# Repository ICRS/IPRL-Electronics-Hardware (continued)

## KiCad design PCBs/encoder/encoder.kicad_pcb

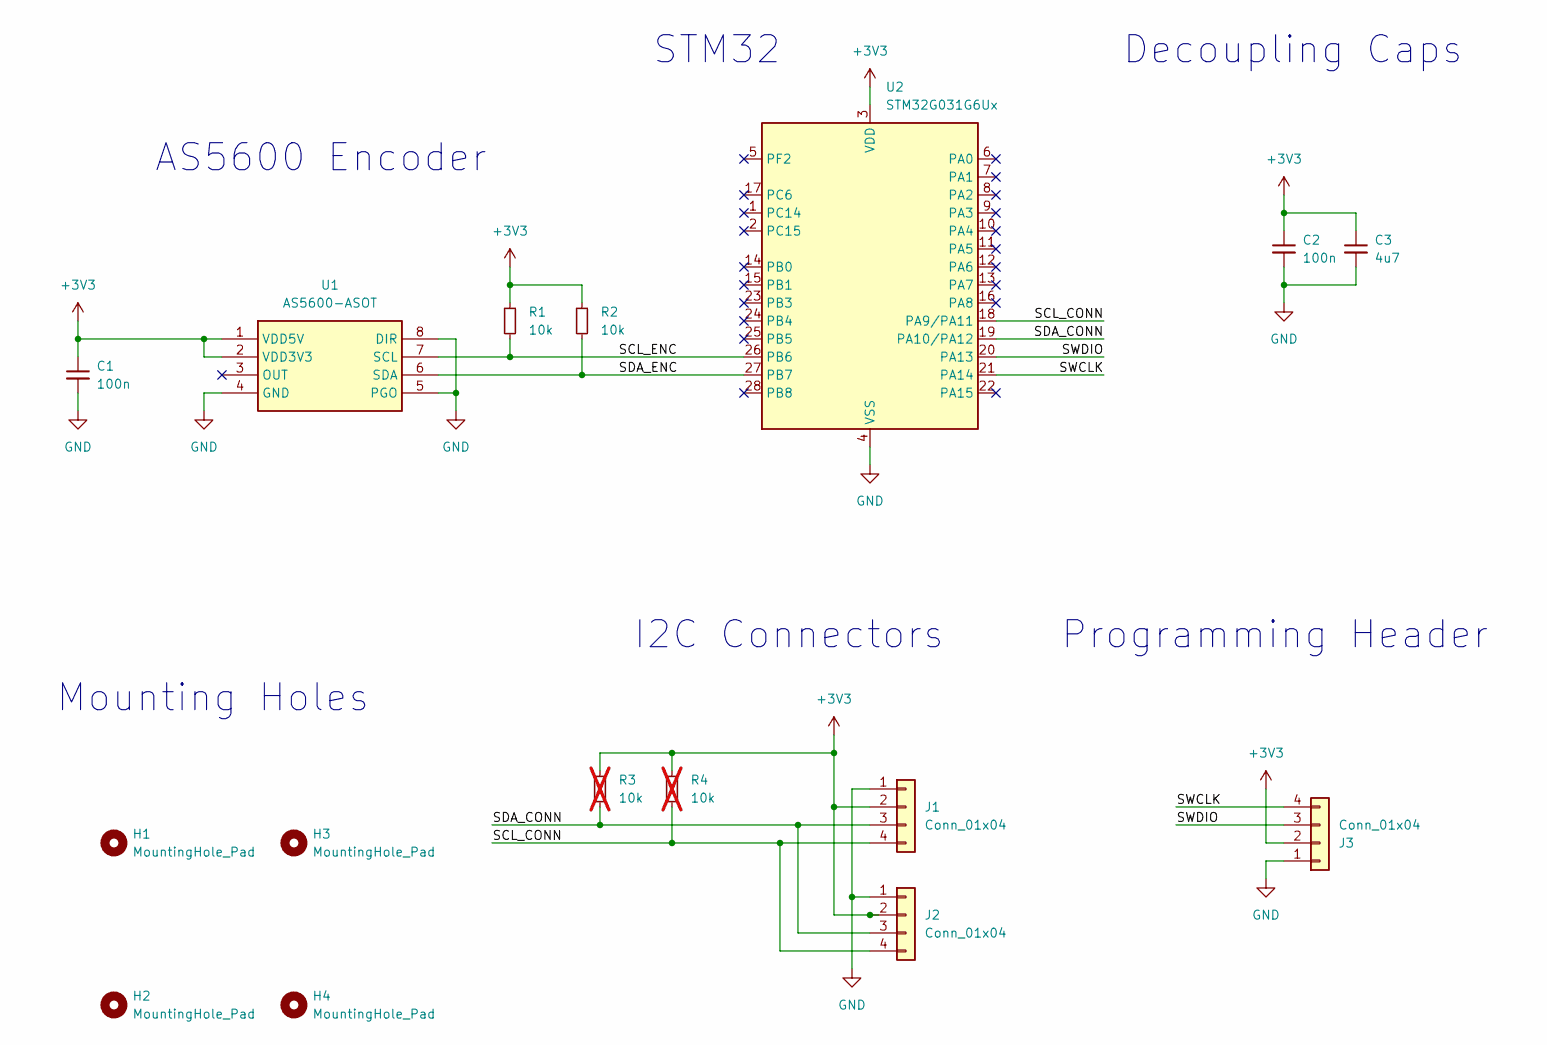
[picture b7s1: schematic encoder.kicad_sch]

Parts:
C1, C2: 100n; C_0603_1608Metric
C3: 4u7; C_0603_1608Metric
H1, H2, H3, H4: MountingHole_Pad; MountingHole_3.2mm_M3
J1, J2: Conn_01x04; JST_XH_B4B-XH-A_1x04_P2.50mm_Vertical
J3: Conn_01x04; JST_GH_SM04B-GHS-TB_1x04-1MP_P1.25mm_Horizontal
R1, R2: 10k; R_0603_1608Metric
R3, R4: 10k; R_0603_1608Metric; not fitted
U1: AS5600-ASOT; SOIC127P600X175-8N; Mouser Part Number 985-AS5600-ASOT
U2: STM32G031G6Ux; QFN-28_4x4mm_P0.5mm

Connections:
+3V3: C1.1, C2.1, C3.1, J1.2, J2.2, J3.2, R1.1, R2.1, R3.1, R4.1, U1.1 (VDD5V), U1.2 (VDD3V3), U2.3 (VDD)
/SCL_CONN: J1.4, J2.4, R4.2, U2.18 (PA9/PA11)
/SCL_ENC: R1.2, U1.7 (SCL), U2.26 (PB6)
/SDA_CONN: J1.3, J2.3, R3.2, U2.19 (PA10/PA12)
/SDA_ENC: R2.2, U1.6 (SDA), U2.27 (PB7)
/SWCLK: J3.4, U2.21 (PA14)
/SWDIO: J3.3, U2.20 (PA13)
GND: C1.2, C2.2, C3.2, J1.1, J2.1, J3.1, U1.4 (GND), U1.5 (PGO), U1.8 (DIR), U2.4 (VSS)

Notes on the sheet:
Mounting Holes
I2C Connectors
STM32
Programming Header
Decoupling Caps
AS5600 Encoder

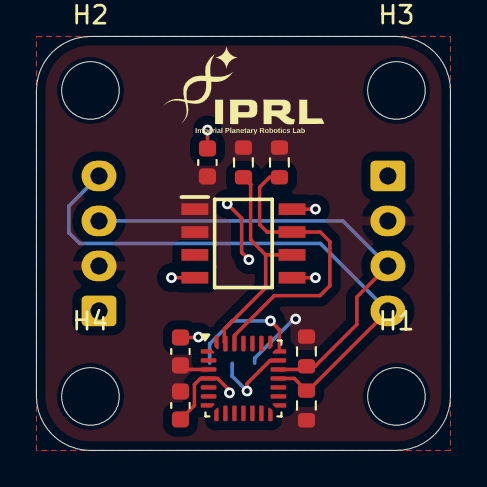
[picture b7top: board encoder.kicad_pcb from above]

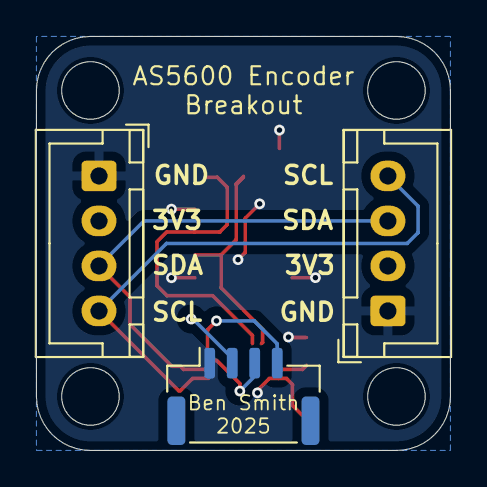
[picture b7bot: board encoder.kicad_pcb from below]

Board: 2 copper layers, 23.0 x 23.0 mm, 16 parts (3 on the bottom side), 8 nets.

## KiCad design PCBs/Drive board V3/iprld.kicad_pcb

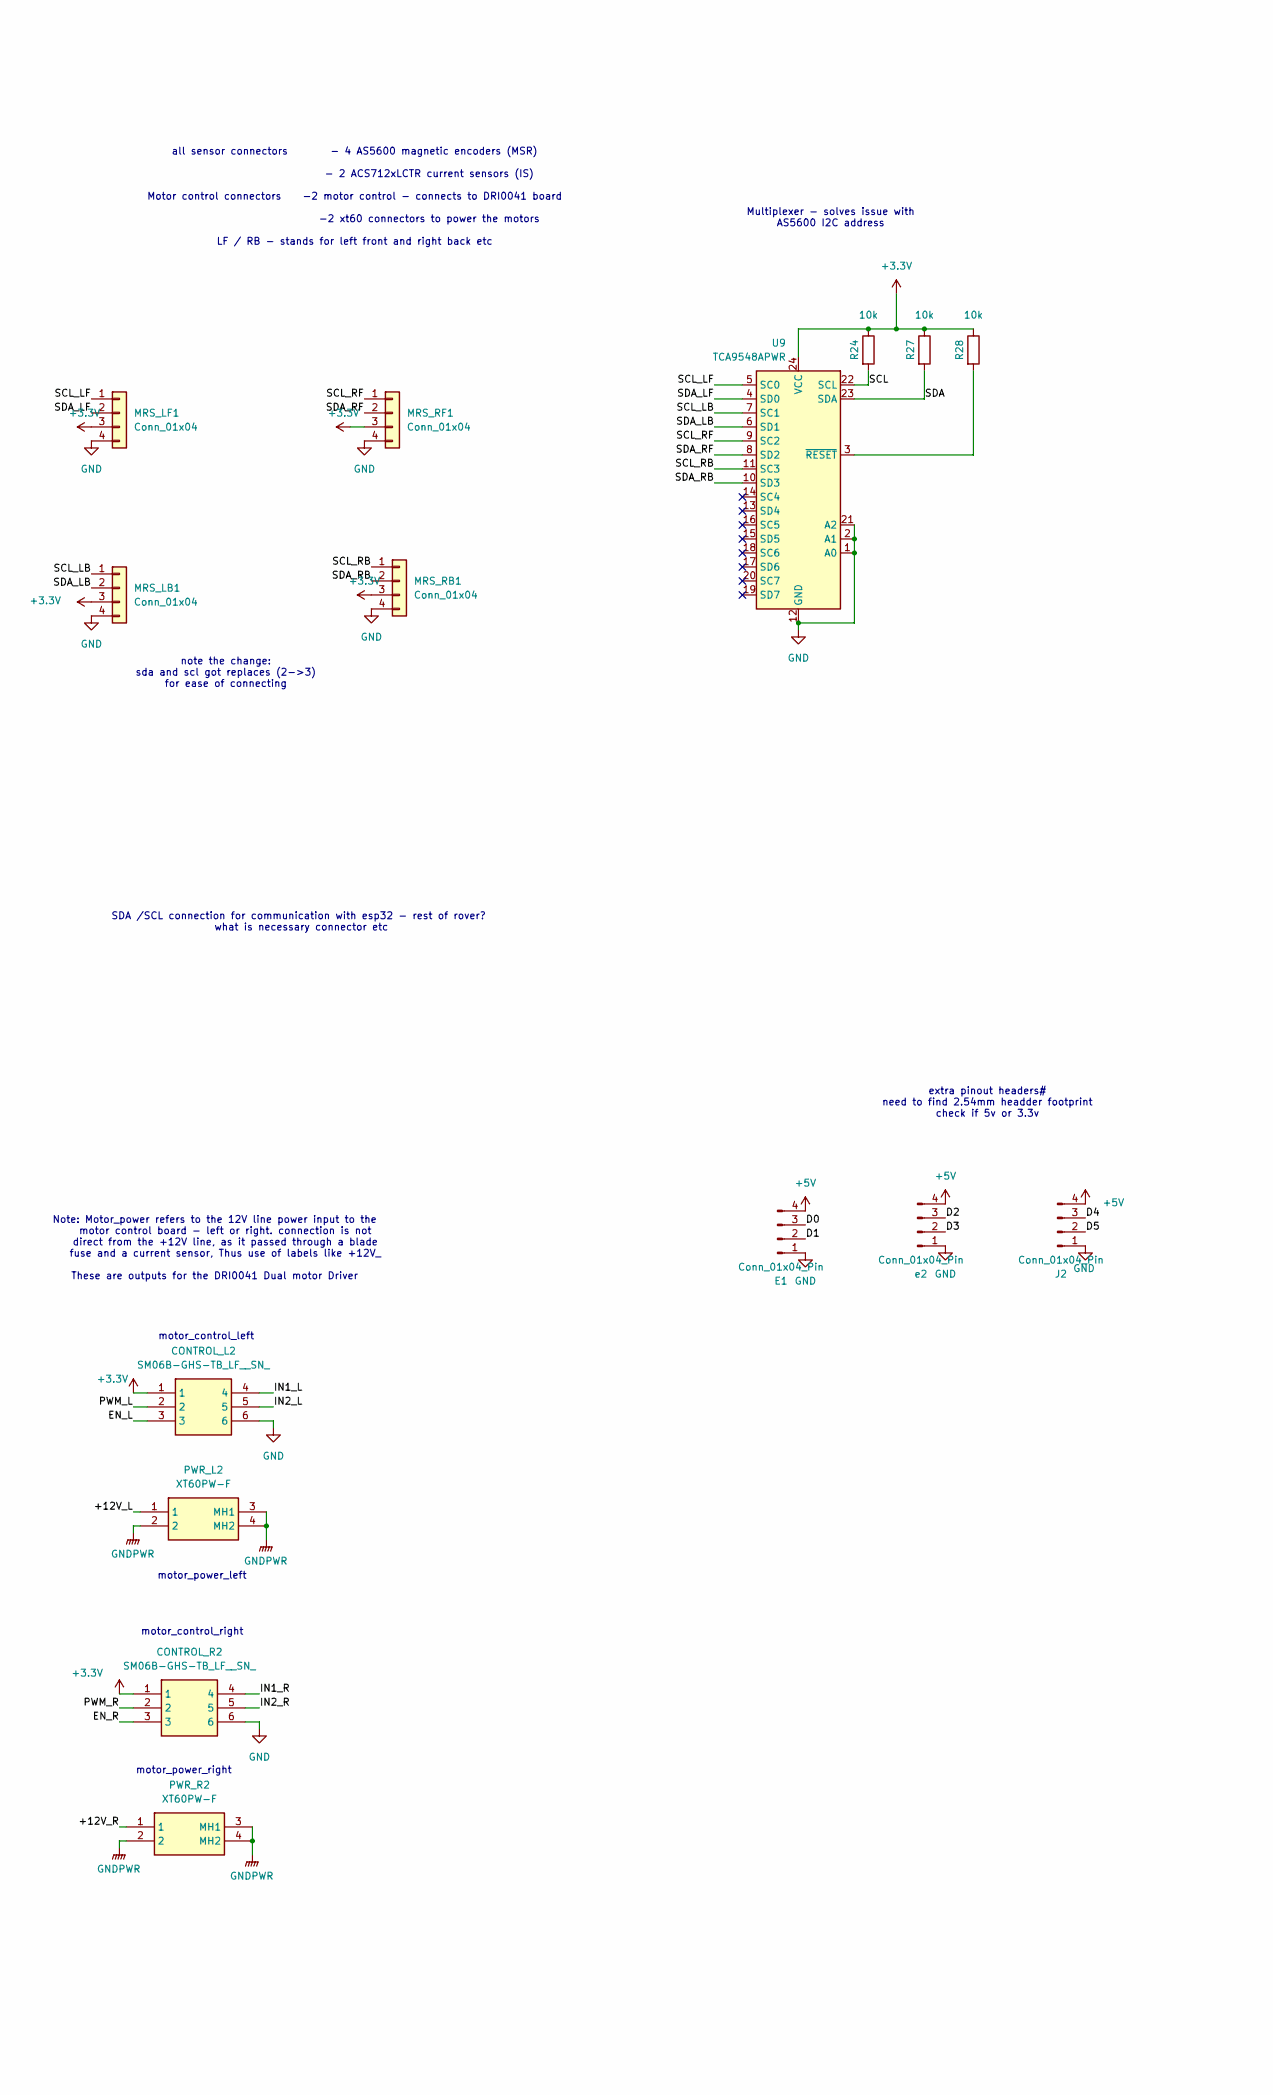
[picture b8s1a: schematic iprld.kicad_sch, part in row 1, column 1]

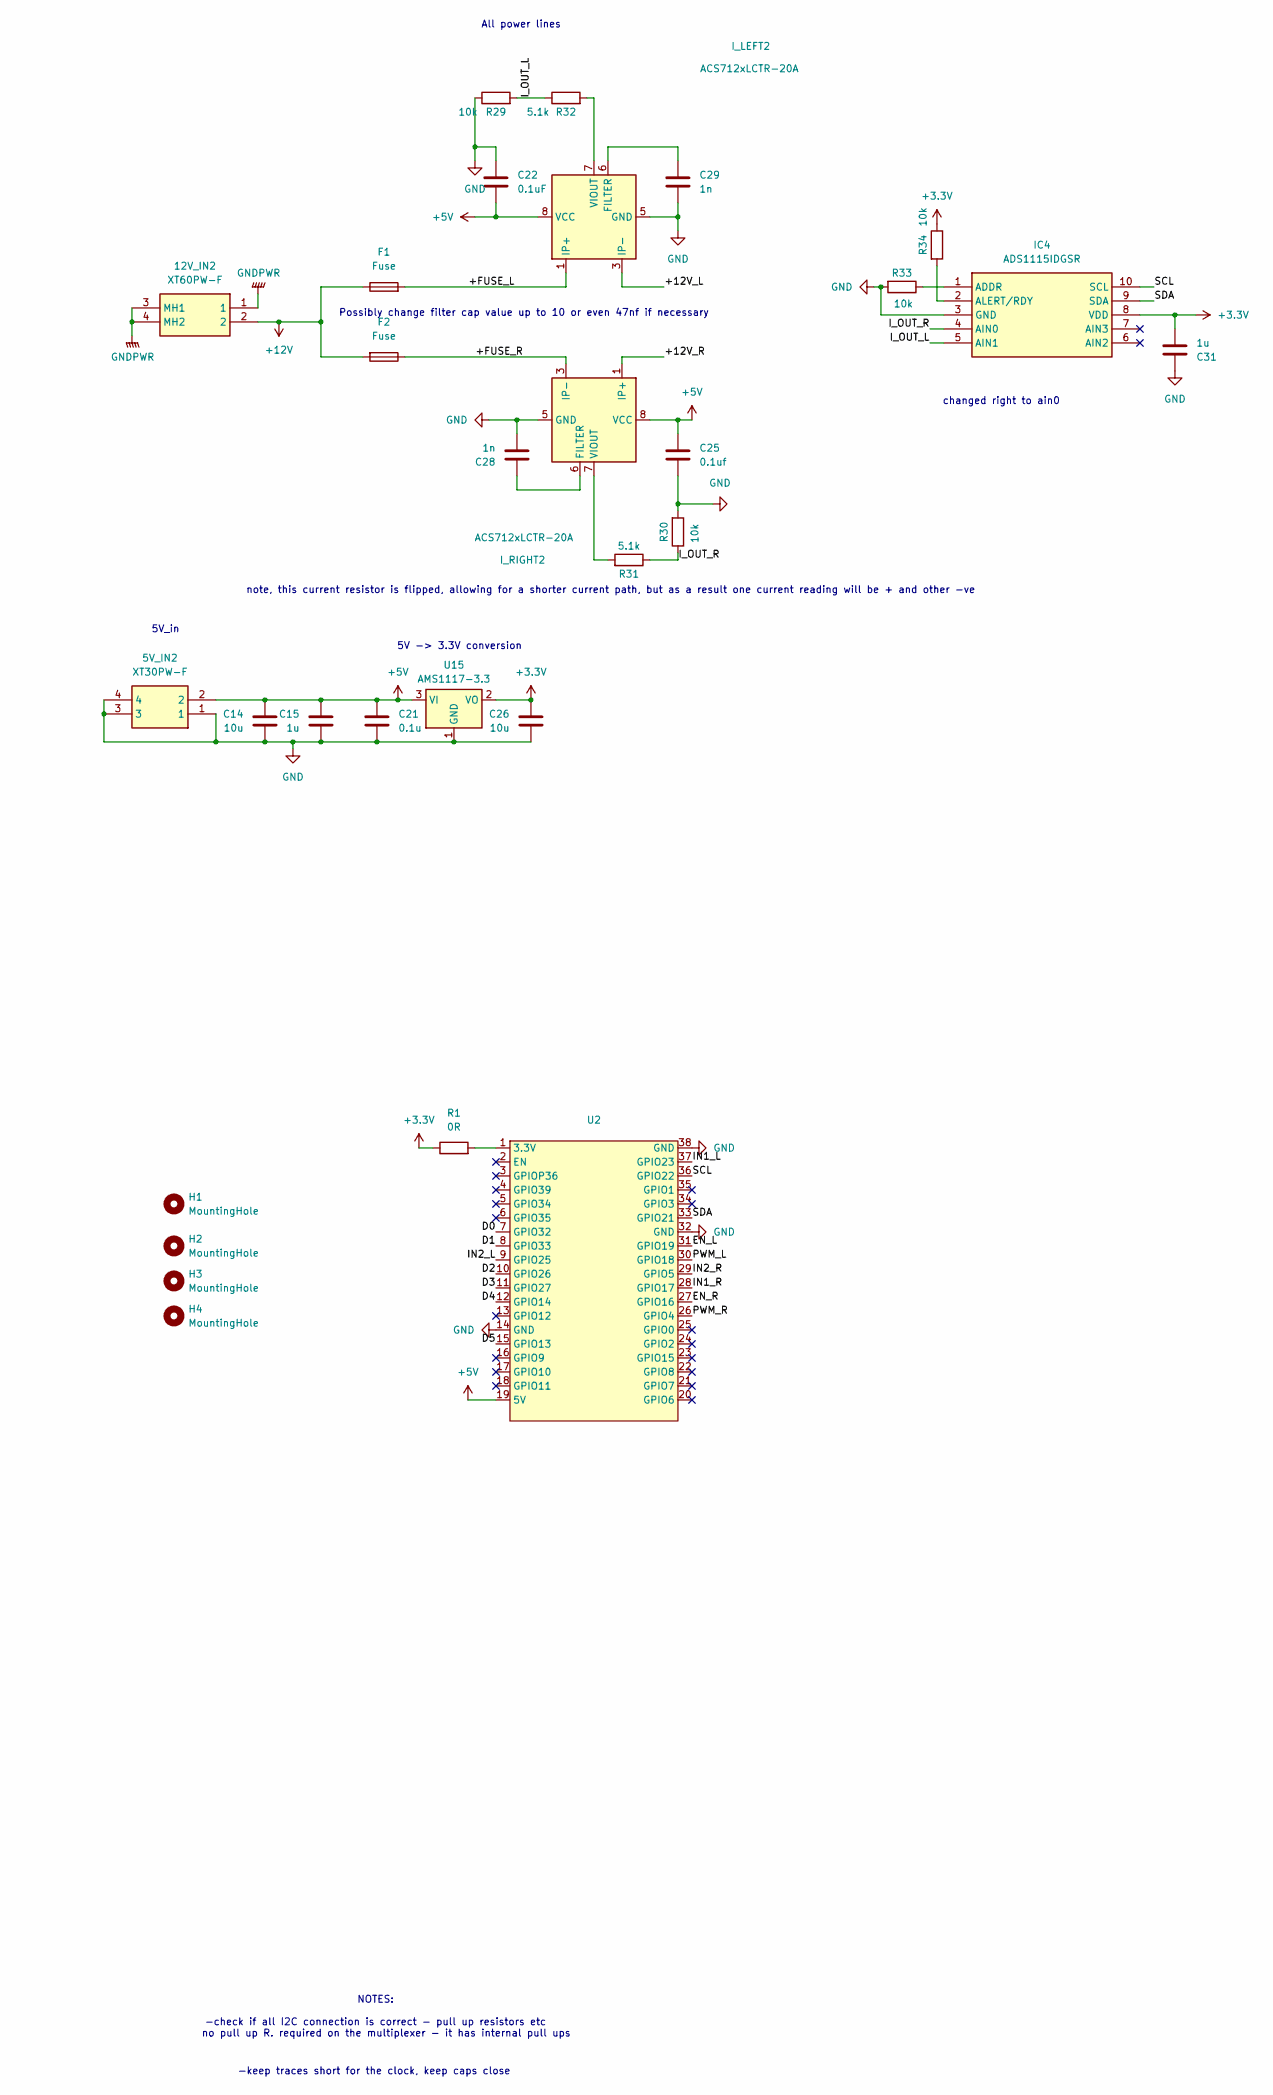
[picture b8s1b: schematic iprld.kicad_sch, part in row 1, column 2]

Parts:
5V_IN2: XT30PW-F; AMASS_XT30PW-M_1x02_P2.50mm_Horizontal; Manufacturer_Part_Number XT30PW-F
12V_IN2: XT60PW-F; AMASS_XT60PW-M_1x02_P7.20mm_Horizontal; Manufacturer_Part_Number XT60PW-F
C14, C26: 10u; C_0805_2012Metric
C15, C31: 1u; C_0805_2012Metric
C21: 0.1u; C_0805_2012Metric
C22: 0.1uF; C_0805_2012Metric
C25: 0.1uf; C_0805_2012Metric
C28, C29: 1n; C_0805_2012Metric
CONTROL_L2: SM06B-GHS-TB_LF__SN_; SM06B-GHS-TB; Manufacturer_Part_Number SM06B-GHS-TB(LF)(SN); Mouser Part Number 306-SM06BGHSTBLFSN
CONTROL_R2: SM06B-GHS-TB_LF__SN_; SM06B-GHS-TB; Manufacturer_Part_Number SM06B-GHS-TB(LF)(SN); Mouser Part Number 306-SM06BGHSTBLFSN
E1: Conn_01x04_Pin; PinHeader_1x04_P2.54mm_Vertical
F1, F2: Fuse; 01530007Z
H1, H2, H3, H4: MountingHole; MountingHole_3.2mm_M3_Pad_TopBottom
IC4: ADS1115IDGSR; SOP50P490X110-10N; Manufacturer_Part_Number ADS1115IDGSR; Mouser Part Number 595-ADS1115IDGSR
I_LEFT2: ACS712xLCTR-20A; SOIC-8_3.9x4.9mm_P1.27mm
I_RIGHT2: ACS712xLCTR-20A; SOIC-8_3.9x4.9mm_P1.27mm
J2: Conn_01x04_Pin; PinHeader_1x04_P2.54mm_Vertical
MRS_LB1: Conn_01x04; JST_GH_BM04B-GHS-TBT_1x04-1MP_P1.25mm_Vertical
MRS_LF1: Conn_01x04; JST_GH_BM04B-GHS-TBT_1x04-1MP_P1.25mm_Vertical
MRS_RB1: Conn_01x04; JST_GH_BM04B-GHS-TBT_1x04-1MP_P1.25mm_Vertical
MRS_RF1: Conn_01x04; JST_GH_BM04B-GHS-TBT_1x04-1MP_P1.25mm_Vertical
PWR_L2: XT60PW-F; XT60PWF; Manufacturer_Part_Number XT60PW-F
PWR_R2: XT60PW-F; XT60PWF; Manufacturer_Part_Number XT60PW-F
R1: 0R; R_0805_2012Metric
R24, R27, R28, R29, R30, R33, R34: 10k; R_0805_2012Metric
R31, R32: 5.1k; R_0805_2012Metric
U2: Z_ESP32_DevKitC_38pin_socket
U9: TCA9548APWR; TSSOP-24_4.4x7.8mm_P0.65mm
U15: AMS1117-3.3; SOT-223-3_TabPin2
e2: Conn_01x04_Pin; PinHeader_1x04_P2.54mm_Vertical

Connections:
+3.3V: C26.1, C31.1, CONTROL_L2.1, CONTROL_R2.1, IC4.8 (VDD), MRS_LB1.3, MRS_LF1.3, MRS_RB1.3, MRS_RF1.3, R1.1, R24.1, R27.1, R28.1, R34.1, U9.24 (VCC), U15.2 (VO)
+5V: 5V_IN2.2, C14.1, C15.1, C21.1, C22.1, C25.1, E1.4, I_LEFT2.8 (VCC), I_RIGHT2.8 (VCC), J2.4, U2.19 (5V), U15.3 (VI), e2.4; also elsewhere on the board
+12V: 12V_IN2.2, F1.1, F2.2; also elsewhere on the board
/+12V_L: I_LEFT2.3 (IP-), I_LEFT2.4 (IP-), PWR_L2.1
/+12V_R: I_RIGHT2.1 (IP+), I_RIGHT2.2 (IP+), PWR_R2.1
/+FUSE_L: F1.2, I_LEFT2.1 (IP+), I_LEFT2.2 (IP+)
/+FUSE_R: F2.1, I_RIGHT2.3 (IP-), I_RIGHT2.4 (IP-)
/D0: E1.3, U2.7 (GPIO32)
/D1: E1.2, U2.8 (GPIO33)
/D2: U2.10 (GPIO26), e2.3
/D3: U2.11 (GPIO27), e2.2
/D4: J2.3, U2.12 (GPIO14)
/D5: J2.2, U2.15 (GPIO13)
/EN_L: CONTROL_L2.3, U2.31 (GPIO19)
/EN_R: CONTROL_R2.3, U2.27 (GPIO16)
/IN1_L: CONTROL_L2.4, U2.37 (GPIO23)
/IN1_R: CONTROL_R2.4, U2.28 (GPIO17)
/IN2_L: CONTROL_L2.5, U2.9 (GPIO25)
/IN2_R: CONTROL_R2.5, U2.29 (GPIO5)
/I_OUT_L: IC4.5 (AIN1), R29.2, R32.1
/I_OUT_R: IC4.4 (AIN0), R30.1, R31.1
/PWM_L: CONTROL_L2.2, U2.30 (GPIO18)
/PWM_R: CONTROL_R2.2, U2.26 (GPIO4)
/SCL: IC4.10 (SCL), R24.2, U2.36 (GPIO22), U9.22 (SCL)
/SCL_LB: MRS_LB1.1, U9.7 (SC1)
/SCL_LF: MRS_LF1.1, U9.5 (SC0)
/SCL_RB: MRS_RB1.1, U9.11 (SC3)
/SCL_RF: MRS_RF1.1, U9.9 (SC2)
/SDA: IC4.9 (SDA), R27.2, U2.33 (GPIO21), U9.23 (SDA)
/SDA_LB: MRS_LB1.2, U9.6 (SD1)
/SDA_LF: MRS_LF1.2, U9.4 (SD0)
/SDA_RB: MRS_RB1.2, U9.10 (SD3)
/SDA_RF: MRS_RF1.2, U9.8 (SD2)
GND: 5V_IN2.1, 5V_IN2.3, 5V_IN2.4, C14.2, C15.2, C21.2, C22.2, C25.2, C26.2, C28.1, C29.1, C31.2, CONTROL_L2.6, CONTROL_R2.6, E1.1, IC4.3 (GND), I_LEFT2.5 (GND), I_RIGHT2.5 (GND), J2.1, MRS_LB1.4, MRS_LF1.4, MRS_RB1.4, MRS_RF1.4, R29.1, R30.2, R33.2, U2.14 (GND), U2.32 (GND), U2.38 (GND), U9.1 (A0), U9.2 (A1), U9.12 (GND), U9.21 (A2), U15.1 (GND), e2.1; also elsewhere on the board
GNDPWR: 12V_IN2.1, 12V_IN2.3 (MH1), 12V_IN2.4 (MH2), PWR_L2.2, PWR_L2.3 (MH1), PWR_L2.4 (MH2), PWR_R2.2, PWR_R2.3 (MH1), PWR_R2.4 (MH2); also elsewhere on the board
unnamed: IC4.1 (ADDR), R33.1
unnamed: IC4.2 (ALERT/RDY), R34.2
unnamed: C29.2, I_LEFT2.6 (FILTER)
unnamed: I_LEFT2.7 (VIOUT), R32.2
unnamed: C28.2, I_RIGHT2.6 (FILTER)
unnamed: I_RIGHT2.7 (VIOUT), R31.2
unnamed: R1.2, U2.1 (3.3V)
unnamed: R28.2, U9.3 (~RESET)

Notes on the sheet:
NOTES: -check if all I2C connection is correct - pull up resistors etc no pull up R. required on the multiplexer - it has internal pull ups
motor_control_left
note, this current resistor is flipped, allowing for a shorter current path, but as a result one current reading will be + and other -ve
Multiplexer - solves issue with AS5600 I2C address
motor_power_left
5V_in
changed right to ain0
all sensor connectors - 4 AS5600 magnetic encoders (MSR) - 2 ACS712xLCTR current sensors (IS) Motor control connectors -2 motor control - connects to DRI0041 board -2 xt60 connectors to power the motors LF / RB - stands for left front and right back etc
SDA /SCL connection for communication with esp32 - rest of rover? what is necessary connector etc
extra pinout headers# need to find 2.54mm headder footprint check if 5v or 3.3v
-keep traces short for the clock, keep caps close
motor_power_right
note the change: sda and scl got replaces (2->3) for ease of connecting
5V -> 3.3V conversion
Note: Motor_power refers to the 12V line power input to the motor control board - left or right. connection is not direct from the +12V line, as it passed through a blade fuse and a current sensor, Thus use of labels like +12V_ These are outputs for the DRI0041 Dual motor Driver
Possibly change filter cap value up to 10 or even 47nf if necessary
motor_control_right
All power lines

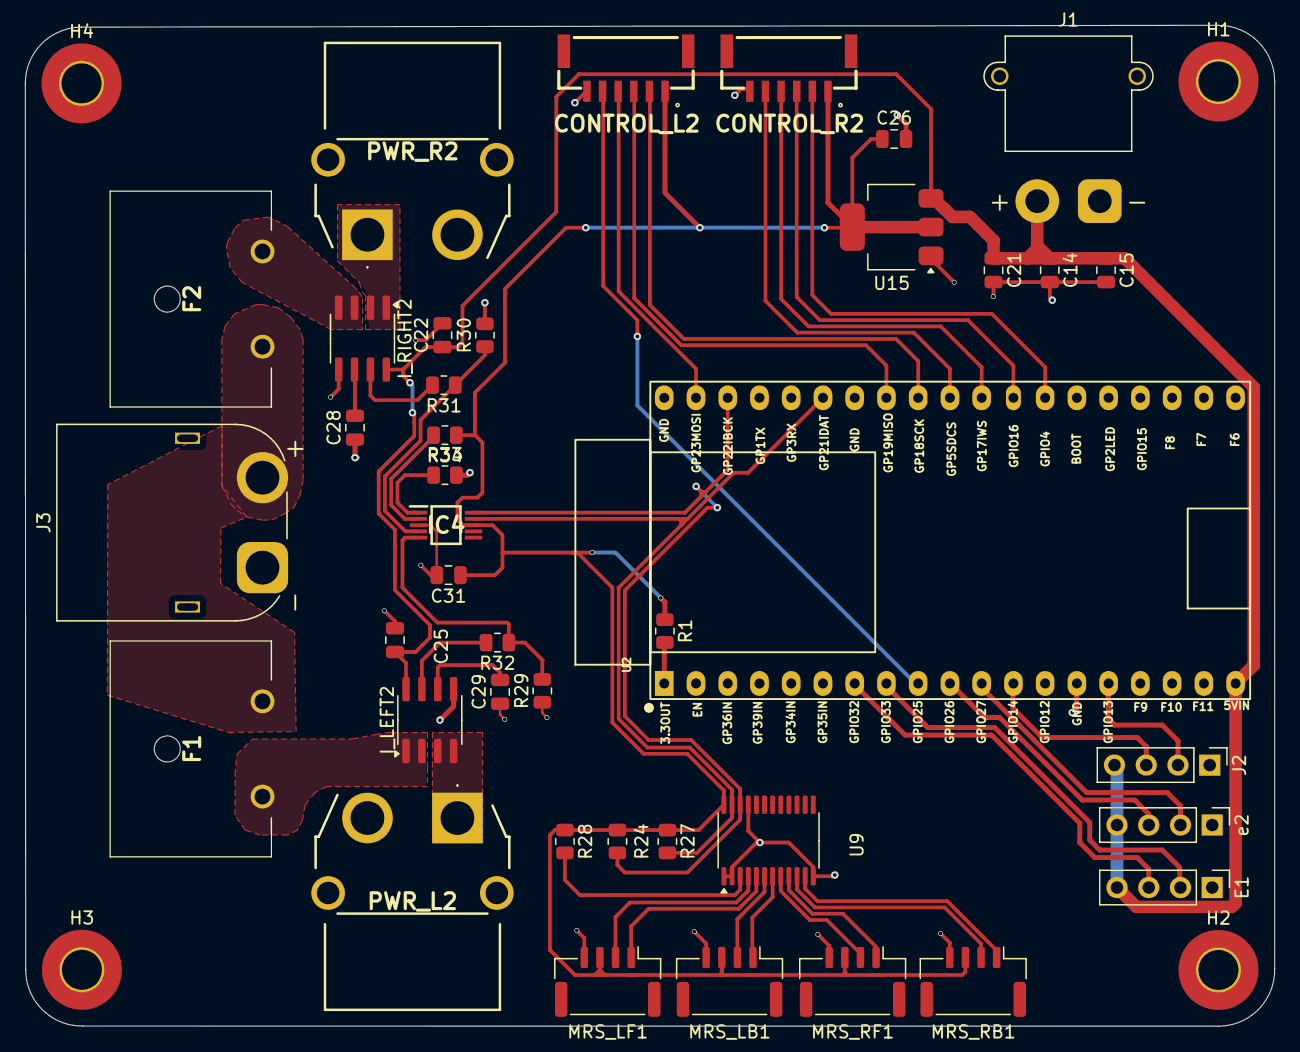
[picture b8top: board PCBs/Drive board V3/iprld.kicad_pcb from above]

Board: 2 copper layers, 100.0 x 80.1 mm, 44 parts (0 on the bottom side), 43 nets.

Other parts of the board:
J1: Conn_01x02; AMASS_XT30PW-M_1x02_P2.50mm_Horizontal
J3: Conn_01x02; AMASS_XT60PW-M_1x02_P7.20mm_Horizontal

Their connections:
+5V: J1.2; also elsewhere on the board
+12V: J3.2; also elsewhere on the board
GND: J1.1; also elsewhere on the board
GNDPWR: J3.1; also elsewhere on the board

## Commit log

2024-12-20 Added KiCad files to gitignore
2024-12-20 Added example AS5600 library
2025-01-15 Arm Project Uploaded
2025-01-15 TEST1 - added a via
2025-01-15 changed 3d model name
2025-01-15 changed adc components
2025-01-15 Added usb C connector
2025-01-15 New USB C footprint, changed XT inputs to male
2025-01-15 added connector names
2025-01-15 Updated Arm PCB
2025-01-15 final small changes - IC2 footprint
2025-01-15 Fixed some DRC errors
2025-01-15 Minor touch ups, arm complete
2025-01-15 Added labels for buttons
2025-01-15 Found some issues in the drive schematic and PCB
2025-01-15 added more decoupling capacitors, fixed flash connections, clock capacitors, thick power traces
2025-01-15 fixed merge issues
2025-01-15 Semi-finished PCB with updated Schematic
2025-01-16 Finished PCB sub mounting holes and fillet
2025-01-16 added potential divider for I_OUT signals
2025-01-16 readded Diode D1, fixed connection issue with SPID and SPIQ
2025-01-16 Small changes to drill PCB
2025-01-16 Switched the LDO to LM317
2025-01-16 Finished Drill PCB
2025-01-17 Manufacturing data created + added names to PCBs.
2025-01-21 first power schematic
2025-03-25 Completed power board
2025-03-26 Second iteration power board
2025-03-27 Power board revisions
2025-03-27 Changes from meeting
2025-03-27 follow up meeting changes
2025-03-27 Meeting follow up changes
2025-03-27 Final copper pour
2025-03-29 Modified output connectors to female
2025-03-29 initial arm power commit
2025-03-30 Replaced fuse holders with 01000064Z
2025-03-30 DRC clean arm connector layout
2025-03-30 DRC clean after fuse holder replacement
2025-04-04 submitted power board
2025-04-22 Main and secondary power board V2
2025-04-23 finished secondary and beginning layout of main
2025-04-23 shortened main board and secondary
2025-04-24 corrected power to main
2025-05-04 main schematic for power board main
2025-05-07 a 5 hour binge of PCB layout on the main
2025-05-08 LEDs added to secondary
2025-05-09 added LED indicators to board and redid power distribution in PCIe
2025-05-12 stitching vias on secondary
2025-05-16 added mounting holes to secondary
2025-05-17 modification to LED switches
2025-05-19 follow up changes from meeting
2025-05-20 Added XT60 splitter
2025-07-05 12 to 5V regulator added
2025-07-05 main board ordered
2025-07-06 stupid breakout board
2025-07-06 Added encoder PCB
2025-07-06 Added Arm Schematic V2
2025-07-07 Add files via upload
    new schematic, changes include
    using esp32 breakout
    magnetic encoder connectors 6x1 -> 4x1
    different fuse footprint
    capacitors are now 0805 footprint
    no optocouplers, isolation and all that came with it
2025-07-07 revised esp32 footprint
2025-07-07 drc clean arm v2
2025-07-07 Add files via upload
    The first try at 3rd gen drive board, with breakout esp32, no isolation and some small fixes. Note, if footprints dont work well, under schematic change footprint name from
    local:Z_ESP32_DevKitC_38pin_socket
    to
    iprl:Z_ESP32_DevKitC_38pin_socket
2025-07-07 arm, drive and power modifications
2025-07-07 fix encoder board fuck you ben
2025-07-07 i2c breakout correction, fuck you Maciej
2025-07-07 changed motor reference to 3.3v
2025-07-07 moved via out the pad, don't worry we like you Samuel
2025-07-07 rounded boards David, someone could cut themselves otherwise
2025-07-07 David half assed the motor reference change and didnt update the layout
2025-07-08 drc clean boards
2025-11-19 Create DRILLTEAMPCBV2YM
2025-11-26 Add files via upload
    11/26/2025: IPRL 2026 motherboard
2025-12-20 Drive Board v5 (25/26 v1)
2025-12-21 Updated drive board
2025-12-21 Drive v5 changes
2025-12-21 Updates drive board
2025-12-21 Found drive board v4 still don't know if it actually ever existed or not
    :(
2025-12-21 Fixed drive board
    had pwm on input only pins :(
2025-12-21 Added termination resistor to drive
    Can be used in event that drive board is used as one end of can bus
2025-12-22 Added esp32 module header footprint
2026-01-18 2025 changes
2026-01-19 Arm V3 Schematic
2026-02-01 Finished arm pcb
2026-02-05 Drive Board V6
    Added for IMU thanks nav :(
2026-02-05 Fixed servo pin and added labels
